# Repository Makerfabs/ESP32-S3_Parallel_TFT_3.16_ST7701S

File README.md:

# ESP32-S3_Parallel_TFT_3.16_ST7701S

This routine how reads the data from the QMI8658 and detects the flip to control the image switching.

## Makerfabs

[Makerfabs home page](https://www.makerfabs.com/)

[Makerfabs Wiki](https://wiki.makerfabs.com/)

## Introduce

Product Link: 

Wiki Link: [https://wiki.makerfabs.com/ESP32-S3_Parallel_TFT_3.16_ST7701S.html](https://wiki.makerfabs.com/ESP32-S3_Parallel_TFT_3.16_ST7701S.html)

The Latest ESP32-S3 3.16 inch display with 320*820 resolution, it integrated display/audio speaker/IMU(QMI8658)/RTC, to make this product ideal for applications such as IoT controlling, electronic photo frame, etc.

## Feature

- Controller: ESP32-S3
- Wireless: WiFi& Bluetooth 5.0
- LCD: 2.8", 320x820 resolution
- LCD Driver: ST7701s
- Flash: 16MB Flash
- PSRAM: 8MB
- USB: 1 * USB to UART
- Power Supply: USB Type-C 5.0V(4.0V~5.25V)
- Button: Flash button and reset button
- MicroSD: Yes
- RTC: Yes
- IMU: Yes
- Microphone input: 1CH INMP441
- Audio output: MAX98357(3.2W@4Ω)
- LVGL support: Yes

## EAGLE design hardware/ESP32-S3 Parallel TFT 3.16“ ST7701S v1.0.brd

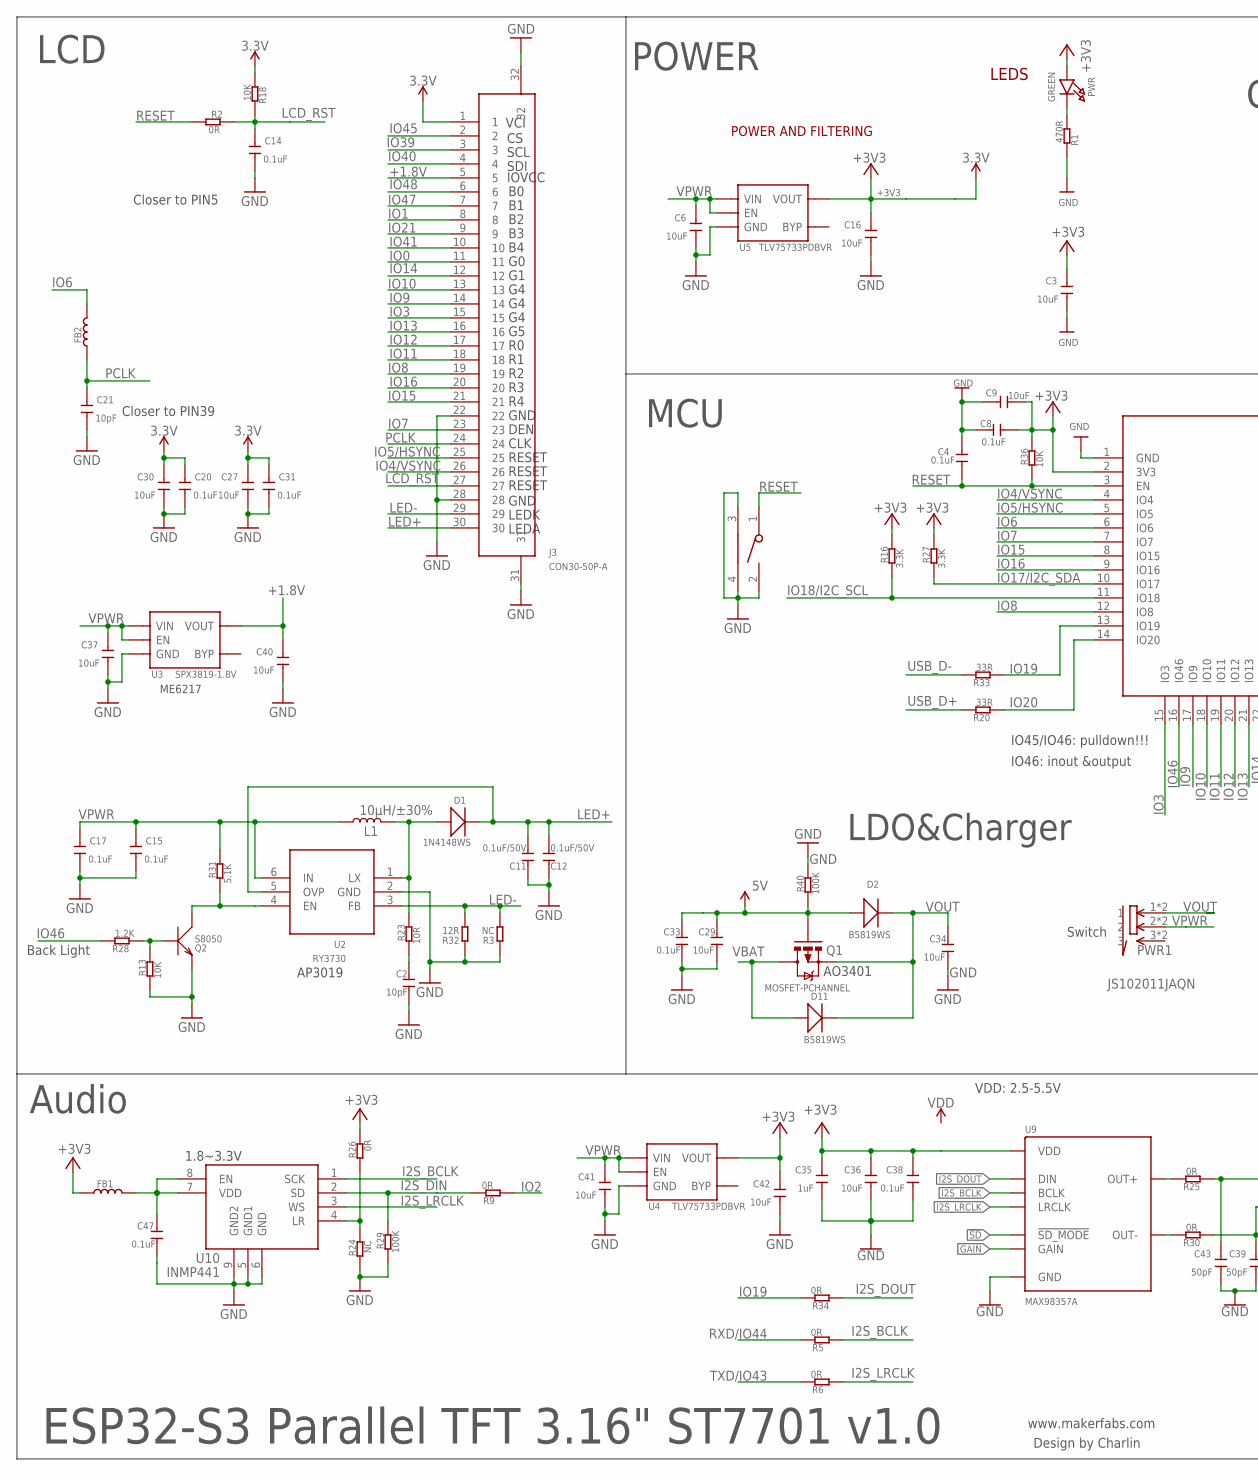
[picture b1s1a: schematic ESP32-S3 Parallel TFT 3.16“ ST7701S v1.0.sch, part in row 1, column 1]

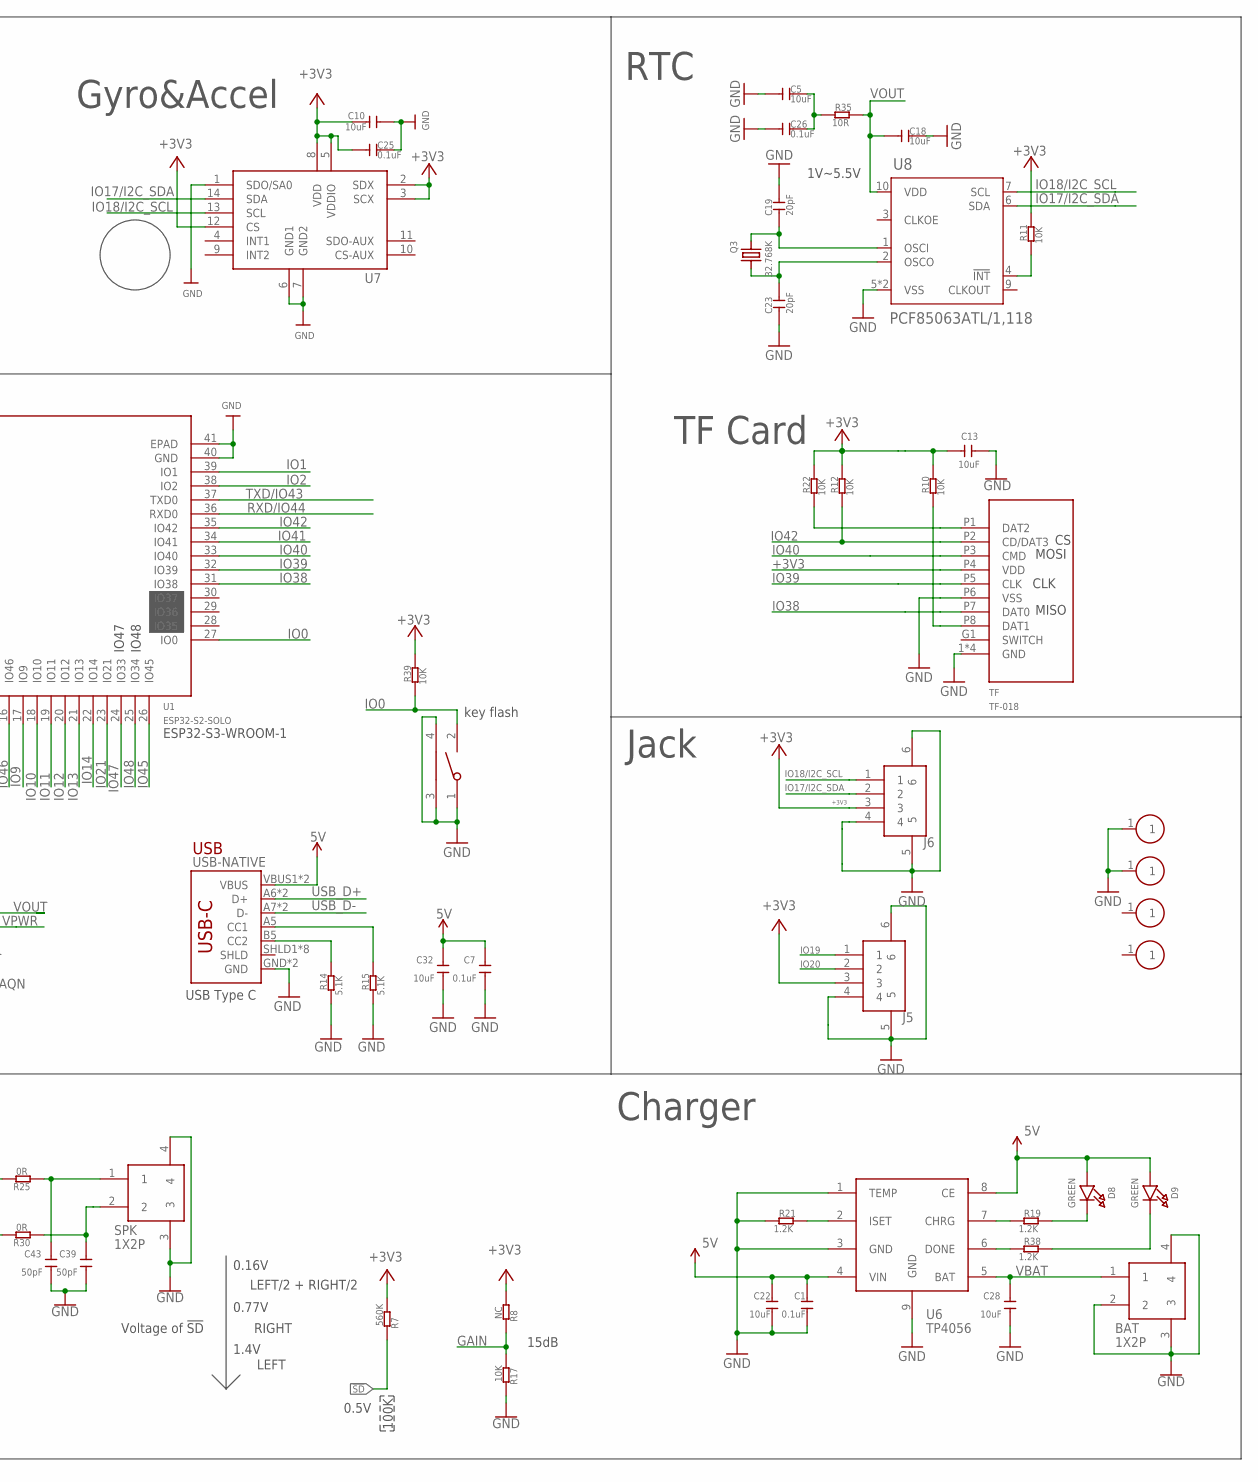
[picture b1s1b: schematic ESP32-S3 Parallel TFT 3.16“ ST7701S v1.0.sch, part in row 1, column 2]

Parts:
BAT: 1X2P; 1X2P-SMT1.25MM
C1, C4, C7, C8, C14, C15, C17, C20, C25, C26, C31, C33, C38, C47: 0.1uF; DISCRETE_C0402
C2, C21: 10pF; DISCRETE_C0402
C3, C5, C6, C9, C10, C13, C16, C18, C22, C27, C28, C29, C30, C32, C34, C36, C37, C40, C41, C42: 10uF; DISCRETE_C0402
C11, C12: 0.1uF/50V; DISCRETE_C0603
C19, C23: 20pF; DISCRETE_C0402
C35: 1uF; DISCRETE_C0402
C39, C43: 50pF; DISCRETE_C0402
D1: 1N4148WS; SOD323
D2, D11: B5819WS; SOD323
D8, D9: GREEN; CHIPLED_0805_NOOUTLINE
FB1, FB2: L'0402'; 0402
FLASH: TS24CA; 2*4*3.5MM
J3: CON30-50P-A; SMD30-50P-1850L540W300H
J5, J6: CON4-100P-V; SMD4-100P-635L374W374H
L1: 10µH/±30%; CR54
PWR: GREEN; CHIPLED_0805_NOOUTLINE
PWR1: JS102011JAQN; SMD-6-2.5MM
Q1: MOSFET-PCHANNEL; SOT23-3
Q2: S8050; SOT23
Q3: 32.768K; XTAL3215
R1: 470R; DISCRETE_R0402
R2, R5, R6, R9, R25, R26, R30, R34: 0R; DISCRETE_R0402
R3: NC; DISCRETE_R0603
R7: 560K; DISCRETE_R0402
R8, R24: NC; DISCRETE_R0402
R10, R11, R12, R13, R17, R18, R22, R36, R39: 10K; DISCRETE_R0402
R14, R15, R31: 5.1K; DISCRETE_R0402
R16, R27: 3.3K; DISCRETE_R0402
R19, R21, R28, R38: 1.2K; DISCRETE_R0402
R20, R33: 33R; DISCRETE_R0402
R23, R35: 10R; DISCRETE_R0402
R29, R40: 100K; DISCRETE_R0402
R32: 12R; DISCRETE_R0603
RST: TS24CA; 2*4*3.5MM
S1, S2, S3, S4: CON1-A; THD1-210M-310D
SPK: 1X2P; 1X2P-SMT1.25MM
TF: TF-018
U1: ESP32­S2­SOLO; ESP32-­S2-­SOLO
U2: RY3730; SOT23-6
U3: SPX3819-1.8V; SOT23-5
U4, U5: TLV75733PDBVR; SOT23-5
U6: TP4056; SOP8-1.27P
U7: QMI8658A; LGA14-50P-300L250W86H
U8: PCF85063ATL/1,118; 10-DFN(2.6X2.6)
U9: MAX98357A; TQFN-16
U10: INMP441; SMD9-105P-472L376W98H
USB-NATIVE: USB_C5; USB-C-16P-5

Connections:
5V: C1.2, C7.2, C22.2, C29.2, C32.2, C33.2, D2.+, D8.A, D9.A, Q1.1 (G), R40.1, U6.4 (VIN), U6.8 (CE), USB-NATIVE.VBUS1 (VBUS), USB-NATIVE.VBUS2 (VBUS)
!SD: R7.2, U9.P$4 (!SD_MODE)
+1.8V: C40.2, J3.5, U3.5 (VOUT)
+3V3: C3.2, C8.1, C9.1, C10.2, C13.2, C16.2, C20.2, C25.2, C27.2, C30.2, C31.2, C35.2, C36.2, C38.2, C42.2, FB1.1, J3.1, J5.3, J6.3, PWR.A, R7.1, R8.1, R10.2, R11.2, R12.2, R16.2, R18.1, R22.2, R26.2, R27.2, R36.2, R39.2, TF.P4 (VDD), U1.2 (3V3), U4.5 (VOUT), U5.5 (VOUT), U7.2 (SDX), U7.3 (SCX), U7.5 (VDDIO), U7.8 (VDD), U7.12 (CS), U9.P$7 (VDD), U9.P$8 (VDD)
GAIN: R8.2, R17.1, U9.P$2 (GAIN)
GND: BAT.2, BAT.3, BAT.4, C1.1, C2.1, C3.1, C4.2, C5.2, C6.1, C7.1, C8.2, C9.2, C10.1, C11.1, C12.1, C13.1, C14.1, C15.1, C16.1, C17.1, C18.1, C19.1, C20.1, C21.1, C22.1, C23.2, C25.1, C26.2, C27.1, C28.1, C29.1, C30.1, C31.1, C32.1, C33.1, C34.1, C35.1, C36.1, C37.1, C38.1, C39.1, C40.1, C41.1, C42.1, C43.1, C47.1, FLASH.1, FLASH.3, FLASH.4, J3.22, J3.28, J3.31, J3.32, J5.4, J5.5, J5.6, J6.4, J6.5, J6.6, Q2.2 (E), R1.2, R3.1, R13.1, R14.1, R15.1, R17.2, R21.1, R24.1, R29.1, R32.1, R40.2, RST.2, RST.3, RST.4, S1.1, S2.1, SPK.3, SPK.4, TF.1 (GND), TF.2 (GND), TF.3 (GND), TF.4 (GND), TF.P6 (VSS), U1.1 (GND), U1.40 (GND), U1.41 (EPAD), U2.2 (GND), U3.2 (GND), U4.2 (GND), U5.2 (GND), U6.1 (TEMP), U6.3 (GND), U6.9 (GND), U7.1 (SDO/SA0), U7.6 (GND1), U7.7 (GND2), U8.5 (VSS), U8.11 (VSS), U9.P$3 (GND), U9.P$11 (GND), U9.P$15 (GND), U9.P$EP (GND), U10.5 (GND1), U10.6 (GND), U10.9 (GND2), USB-NATIVE.GND, USB-NATIVE.GND2 (GND)
I2S_BCLK: R5.1, U9.P$16 (BCLK), U10.1 (SCK)
I2S_DIN: R9.2, R29.2, U10.2 (SD)
I2S_DOUT: R34.1, U9.P$1 (DIN)
I2S_LRCLK: R6.1, U9.P$14 (LRCLK), U10.3 (WS)
IO0: FLASH.2, J3.11, R39.1, U1.27 (IO0)
IO1: J3.8, U1.39 (IO1)
IO2: R9.1, U1.38 (IO2)
IO3: J3.15, U1.15 (IO3)
IO4/VSYNC: J3.26, U1.4 (IO4)
IO5/HSYNC: J3.25, U1.5 (IO5)
IO6: FB2.2, U1.6 (IO6)
IO7: J3.23, U1.7 (IO7)
IO8: J3.19, U1.12 (IO8)
IO9: J3.14, U1.17 (IO9)
IO10: J3.13, U1.18 (IO10)
IO11: J3.18, U1.19 (IO11)
IO12: J3.17, U1.20 (IO12)
IO13: J3.16, U1.21 (IO13)
IO14: J3.12, U1.22 (IO14)
IO15: J3.21, U1.8 (IO15)
IO16: J3.20, U1.9 (IO16)
IO17/I2C_SDA: J6.2, R27.1, U1.10 (IO17), U7.14 (SDA), U8.6 (SDA)
IO18/I2C_SCL: J6.1, R16.1, U1.11 (IO18), U7.13 (SCL), U8.7 (SCL)
IO19: J5.1, R33.1, R34.2, U1.13 (IO19)
IO20: J5.2, R20.1, U1.14 (IO20)
IO21: J3.9, U1.23 (IO21)
IO38: TF.P7 (DAT0), U1.31 (IO38)
IO39: J3.3, TF.P5 (CLK), U1.32 (IO39)
IO40: J3.4, TF.P3 (CMD), U1.33 (IO40)
IO41: J3.10, U1.34 (IO41)
IO42: R12.1, TF.P2 (CD/DAT3), U1.35 (IO42)
IO45: J3.2, U1.26 (IO45)
IO46: R28.2, U1.16 (IO46)
IO47: J3.7, U1.24 (IO33)
IO48: J3.6, U1.25 (IO34)
LCD_RST: C14.2, J3.27, R2.2, R18.2
LED+: C11.2, C12.2, D1.-, J3.30, U2.5 (OVP)
LED-: J3.29, R3.2, R32.2, U2.3 (FB)
unnamed: R22.1, TF.P1 (DAT2)
unnamed: R10.1, TF.P8 (DAT1)
unnamed: C5.1, C26.1, R35.1
unnamed: C19.2, Q3.P$1 (1), U8.1 (OSCI)
unnamed: R30.2, U9.P$10 (OUT-)
unnamed: R15.2, USB-NATIVE.A5 (CC1)
unnamed: PWR.C, R1.1
unnamed: Q2.1 (B), R13.2, R28.1
unnamed: C39.2, R30.1, SPK.2
unnamed: R24.2, R26.1, U10.4 (LR)
unnamed: C47.2, FB1.2, U10.7 (VDD), U10.8 (EN)
unnamed: R11.1, U8.4 (!INT)
unnamed: C23.1, Q3.P$2 (2), U8.2 (OSCO)
unnamed: R14.2, USB-NATIVE.B5 (CC2)
unnamed: C43.2, R25.1, SPK.1
unnamed: D1.+, L1.P$2 (2), R23.2, U2.1 (LX)
unnamed: R25.2, U9.P$9 (OUT+)
unnamed: C2.2, R23.1
unnamed: R21.2, U6.2 (ISET)
unnamed: Q2.3 (C), R31.1, U2.4 (EN)
unnamed: R19.1, U6.7 (CHRG)
unnamed: R38.1, U6.6 (DONE)
unnamed: D8.C, R19.2
unnamed: D9.C, R38.2
PCLK: C21.2, FB2.1, J3.24
RESET: C4.1, R2.1, R36.1, RST.1, U1.3 (EN)
RXD/IO44: R5.2, U1.36 (RXD0)
TXD/IO43: R6.2, U1.37 (TXD0)
USB_D+: R20.2, USB-NATIVE.A6 (D+), USB-NATIVE.B6 (D+)
USB_D-: R33.2, USB-NATIVE.A7 (D-), USB-NATIVE.B7 (D-)
VBAT: BAT.1, C28.2, D11.+, Q1.3 (D), U6.5 (BAT)
VOUT: C18.2, C34.2, D2.-, D11.-, PWR1.1, PWR1.1@1 (1), Q1.2 (S), R35.2, U8.10 (VDD)
VPWR: C6.2, C15.2, C17.2, C37.2, C41.2, L1.P$1 (1), PWR1.2, PWR1.2@1 (2), R31.2, U2.6 (IN), U3.1 (VIN), U3.3 (EN), U4.1 (VIN), U4.3 (EN), U5.1 (VIN), U5.3 (EN)

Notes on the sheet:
www.makerfabs.com
Design by Charlin
LEDS
POWER AND FILTERING
ESP32-S3 Parallel TFT 3.16" ST7701 v1.0
POWER
RTC
Back Light
IO45/IO46: pulldown!!!
IO46: inout &output
USB
USB Type C
Jack
LCD
MCU
ESP32-S3-WROOM-1
IO47
IO48
Closer to PIN5
AP3019
Closer to PIN39
LDO&Charger
AO3401
VCI
LEDA
LEDK
GND
RESET
CLK
DEN
IOVCC
SDI
SCL
ME6217
key flash
TF Card
1V~5.5V
Switch
Gyro&Accel
VDD: 2.5-5.5V

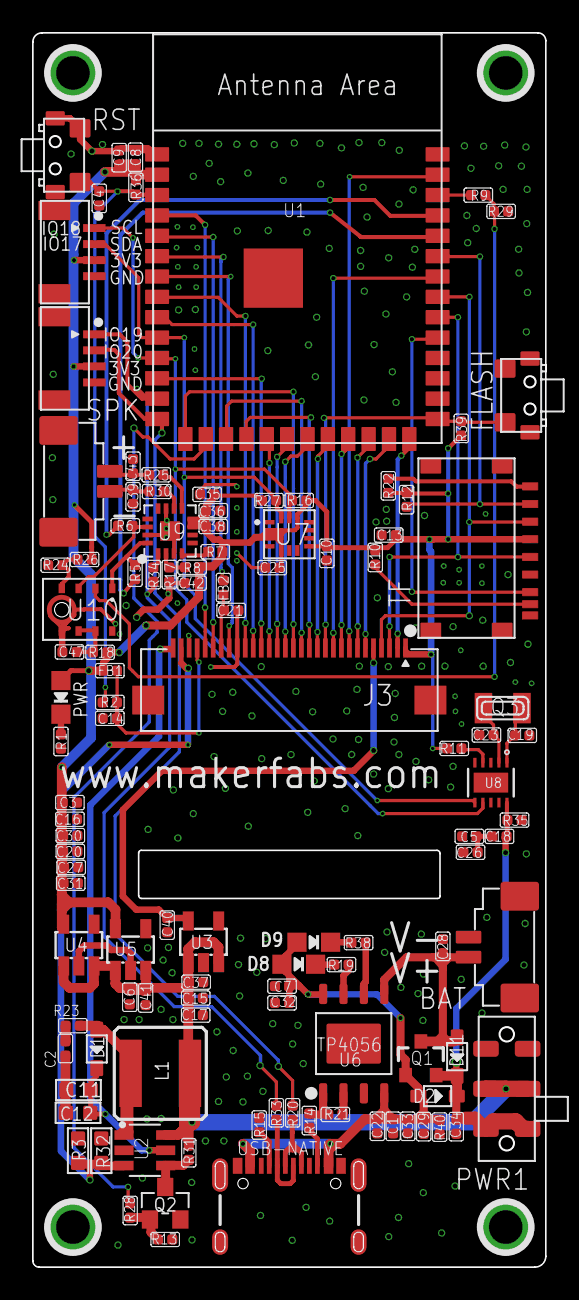
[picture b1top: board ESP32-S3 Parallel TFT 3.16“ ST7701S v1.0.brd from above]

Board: 2 copper layers, 32.0 x 77.0 mm, 118 parts (1 on the bottom side), 77 nets.

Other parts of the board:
U$1: MAKERFABS_0.3

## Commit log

2025-10-23 init
2025-10-24 add lvgl9 example
2025-10-24 add weather example
2025-10-28 add record example

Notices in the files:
parts and their libraries:
microbuilder: This work is placed in the public domain, and may be freely used for commercial and non-commercial work with the following conditions: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
SparkFun-Coils: Licensing: Creative Commons ShareAlike 4.0 International - https://creativecommons.org/licenses/by-sa/4.0
